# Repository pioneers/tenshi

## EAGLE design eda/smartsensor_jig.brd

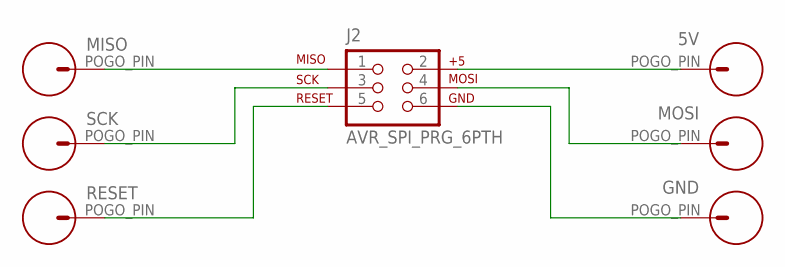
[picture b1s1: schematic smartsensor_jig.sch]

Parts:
5V: POGO_PIN; POGO_PIN_394
GND: POGO_PIN; POGO_PIN_394
J2: AVR_SPI_PRG_6PTH; 2X3
MISO: POGO_PIN; POGO_PIN_394
MOSI: POGO_PIN; POGO_PIN_394
RESET: POGO_PIN; POGO_PIN_394
SCK: POGO_PIN; POGO_PIN_394

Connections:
5V: 5V.POGO_PIN, J2.2
GND: GND.POGO_PIN, J2.6
MISO: J2.1, MISO.POGO_PIN
MOSI: J2.4, MOSI.POGO_PIN
RESET: J2.5, RESET.POGO_PIN
SCK: J2.3, SCK.POGO_PIN

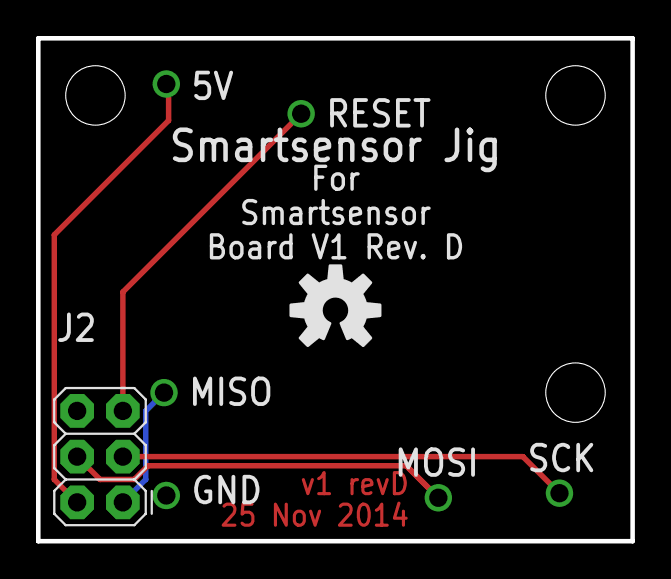
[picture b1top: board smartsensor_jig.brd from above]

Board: 2 copper layers, 33.0 x 27.9 mm, 12 parts (1 on the bottom side), 6 nets.

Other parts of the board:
U$1: OSHW-LOGO-M
U$2: PIE-LOGO-SMALL
U$3, U$4, U$5: STAND-OFF

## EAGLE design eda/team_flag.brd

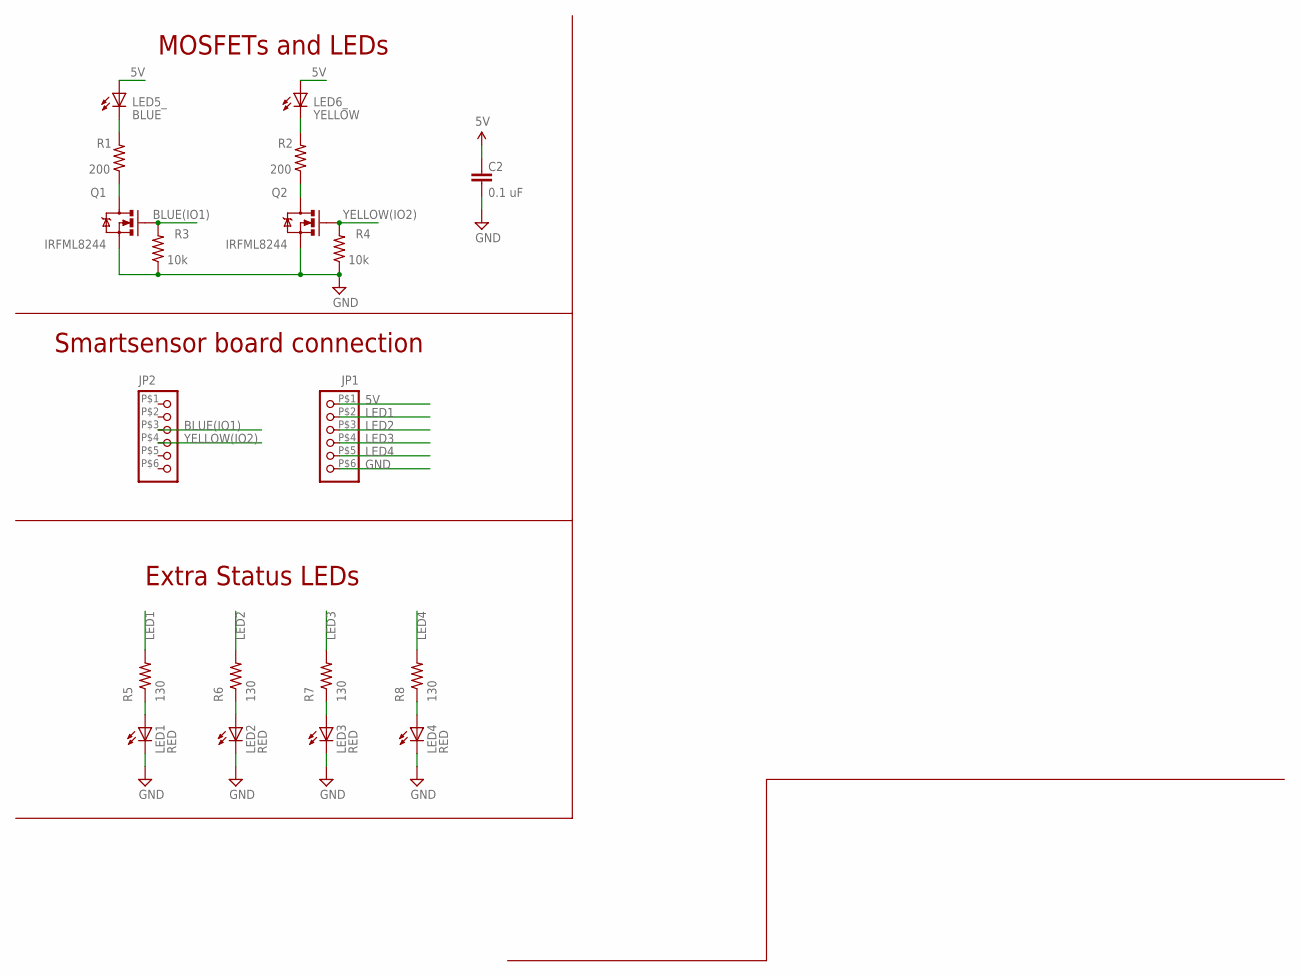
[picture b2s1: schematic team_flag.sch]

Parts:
C2: 0.1 uF; 0603-CAP
JP1, JP2: PINHD-1X6SMD-C; 1X06-SMD-C
LED1, LED2, LED3, LED4: RED; LED-0805
LED5_: BLUE; LED5MM-NOFLAT
LED6_: YELLOW; LED5MM-NOFLAT
Q1, Q2: IRFML8244; SOT23-3
R1, R2: 200; R0603
R3, R4: 10k; R0603
R5, R6, R7, R8: 130; R0603

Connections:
5V: C2.1, JP1.P$1 (1), LED5_.A, LED6_.A
BLUE(IO1): JP2.P$3 (3), Q1.1 (G), R3.2
BSOURCE: Q1.3 (D), R1.1
GND: C2.2, JP1.P$6 (6), LED1.C, LED2.C, LED3.C, LED4.C, Q1.2 (S), Q2.2 (S), R3.1, R4.1
LED1: JP1.P$2 (2), R5.2
LED2: JP1.P$3 (3), R6.2
LED3: JP1.P$4 (4), R7.2
LED4: JP1.P$5 (5), R8.2
unnamed: LED2.A, R6.1
unnamed: LED5_.K (C), R1.2
unnamed: LED6_.K (C), R2.2
unnamed: LED1.A, R5.1
unnamed: LED3.A, R7.1
unnamed: LED4.A, R8.1
YELLOW(IO2): JP2.P$4 (4), Q2.1 (G), R4.2
YSOURCE: Q2.3 (D), R2.1

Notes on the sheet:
MOSFETs and LEDs
Smartsensor board connection
Extra Status LEDs

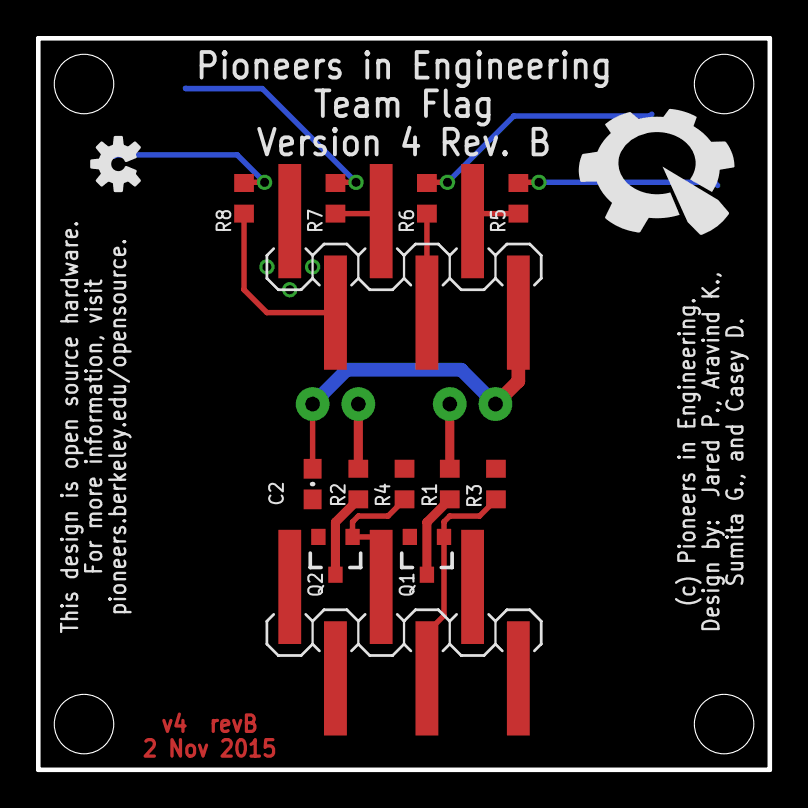
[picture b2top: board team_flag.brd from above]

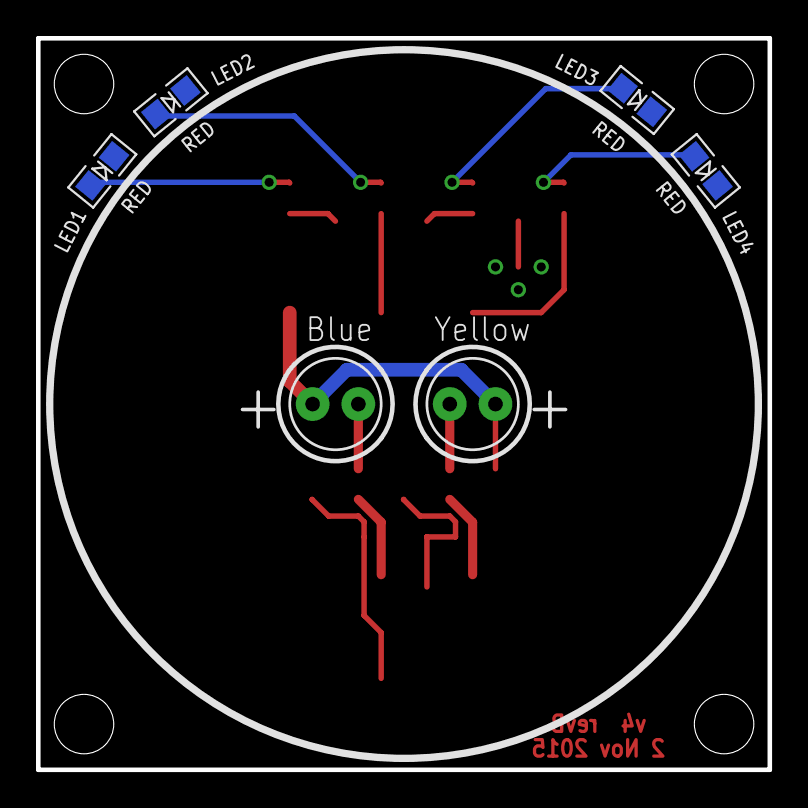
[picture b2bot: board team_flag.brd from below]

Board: 2 copper layers, 40.6 x 40.6 mm, 25 parts (6 on the bottom side), 16 nets.

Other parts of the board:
U$1: PIE-LOGO-SMALL
U$2: OSHW-LOGO-S
U$11, U$12, U$13, U$14: STAND-OFF

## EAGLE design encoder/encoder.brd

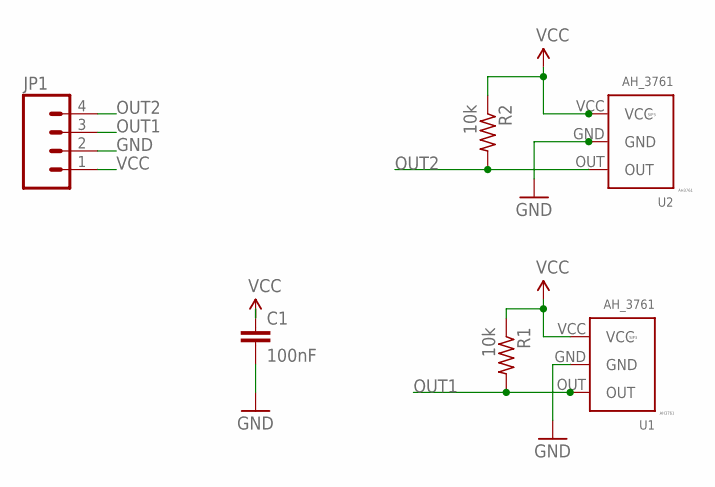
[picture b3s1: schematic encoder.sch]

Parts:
C1: 100nF; 0603-CAP
JP1: M04POLAR; MOLEX-1X4
R1, R2: 10k; R0603
U1, U2: AH_3761; SIP3

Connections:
GND: C1.2, JP1.2, U1.GND, U2.GND
OUT1: JP1.3, R1.2, U1.OUT
OUT2: JP1.4, R2.2, U2.OUT
VCC: C1.1, JP1.1, R1.1, R2.1, U1.VCC, U2.VCC

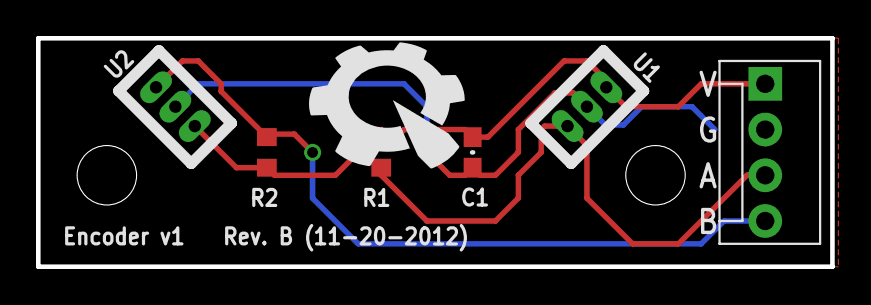
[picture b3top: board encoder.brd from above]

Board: 2 copper layers, 44.1 x 12.7 mm, 10 parts (1 on the bottom side), 4 nets.

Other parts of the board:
E$1, E$2: STAND-OFF
U$1: PIE-LOGO-SMALL
U$2: OSHW-LOGO-S

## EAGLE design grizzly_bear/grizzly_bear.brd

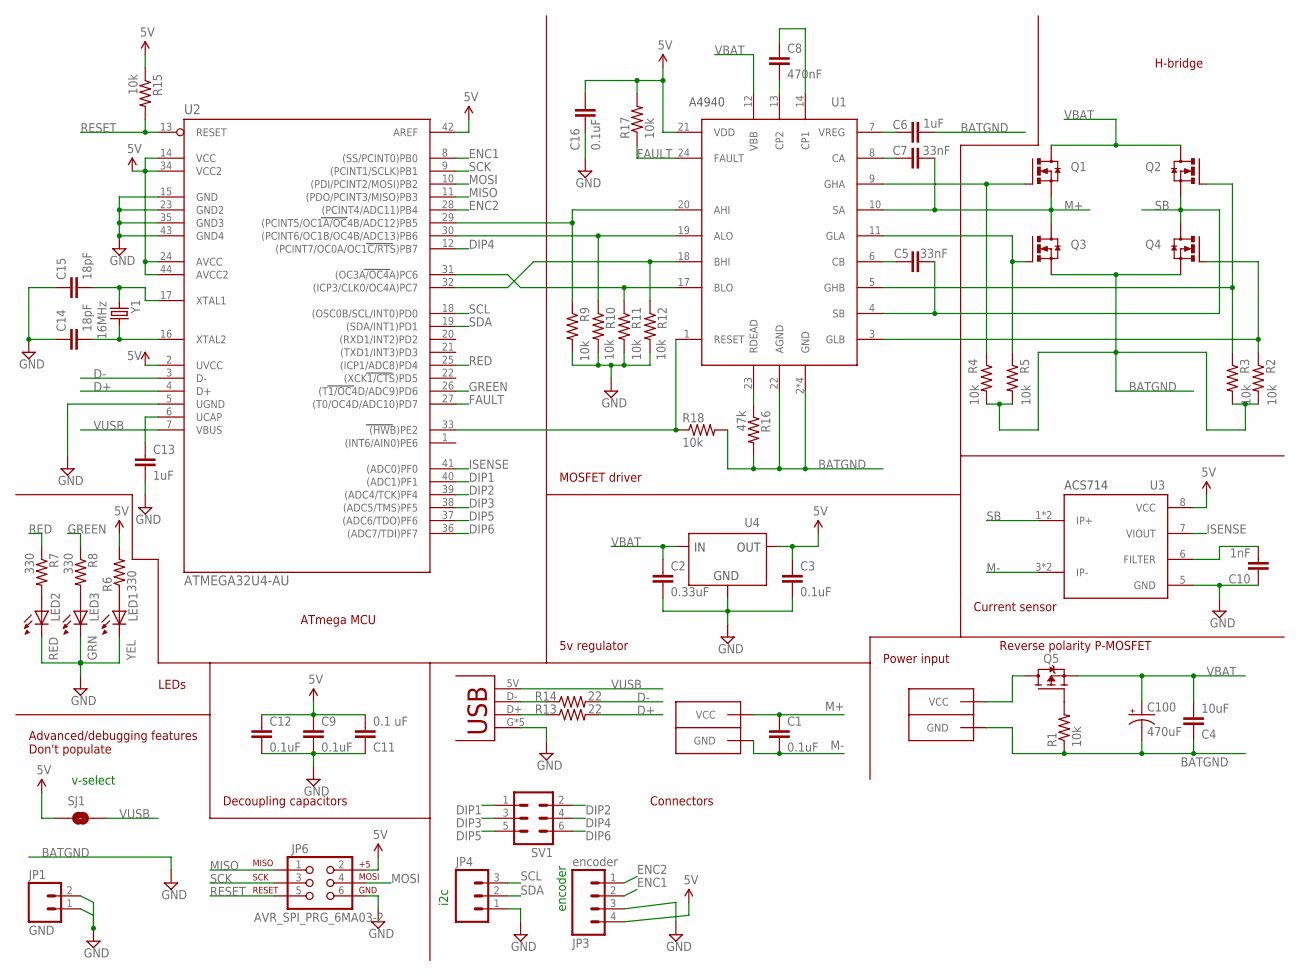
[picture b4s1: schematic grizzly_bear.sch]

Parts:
C1, C3, C9, C12, C16: 0.1uF; 0603-CAP
C2: 0.33uF; 0603-CAP
C4: 10uF; 0603-CAP
C5, C7: 33nF; 0603-CAP
C6, C13: 1uF; 0603-CAP
C8: 470nF; 0603-CAP
C10: 1nF; 0603-CAP
C11: 0.1 uF; 0603-CAP
C14, C15: 18pF; 0603-CAP
C100: 470uF; PANASONIC_G
JP1: GND; 1X02
JP3: encoder; 1X04-MTA
JP4: M031X03-MTA; 1X03-MTA
JP6: AVR_SPI_PRG_6MA03-2; MA03-2
LED1: YEL; LED-0805
LED2: RED; LED-0805
LED3: GRN; LED-0805
Q1, Q2, Q3, Q4: N-CHANNEL-MOSFET; SOT669
Q5: IPD90P03P4L; TO252
R1, R2, R3, R4, R5, R9, R10, R11, R12, R15, R17, R18: 10k; R0603
R6, R7, R8: 330; R0603
R13, R14: 22; R0603
R16: 47k; R0603
SJ1: SOLDERJUMPERNO; SJ_2S-NO
SV1: MA03-2
U1: A4940; 24-PIN_TSSOP
U2: ATMEGA32U4-AU; TQFP44
U3: ACS714; 8-PIN_SOIC
U4: UA78L00; SOT-89-3
U$2: USB-M26FTR
U$18, U$19: ANDERSONVERTICAL; ANDERSON_VERTICAL
Y1: 16MHz; HC49UP

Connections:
5V: C3.1, C9.1, C11.2, C12.1, C16.1, JP3.4, JP6.2, R6.2, R15.1, R17.2, SJ1.1, U1.21 (VDD), U2.2 (UVCC), U2.14 (VCC), U2.24 (AVCC), U2.34 (VCC2), U2.42 (AREF), U2.44 (AVCC2), U3.8 (VCC), U4.OUTPUT (OUT); also elsewhere on the board
AHI: R9.1, U1.20 (AHI), U2.29 ((PCINT5/OC1A/OC4B/ADC12)PB5)
ALO: R10.1, U1.19 (ALO), U2.30 ((PCINT6/OC1B/OC4B/ADC13)PB6)
BHI: R12.1, U1.18 (BHI), U2.32 ((ICP3/CLK0/OC4A)PC7)
BLO: R11.1, U1.17 (BLO), U2.31 ((OC3A/OC4A)PC6)
CA: C7.1, U1.8 (CA)
CB: C5.2, U1.6 (CB)
CP1: C8.1, U1.14 (CP1)
CP2: C8.2, U1.13 (CP2)
D+: R13.2, U2.4 (D+)
D+-_CON: R13.1, U$2.D+
D-: R14.2, U2.3 (D-)
D-_CON: R14.1, U$2.D-
DE: U2.1 ((INT6/AIN0)PE6); also elsewhere on the board
DIP1: SV1.1, U2.40 ((ADC1)PF1)
DIP2: SV1.2, U2.39 ((ADC4/TCK)PF4)
DIP3: SV1.3, U2.38 ((ADC5/TMS)PF5)
DIP4: SV1.4, U2.12 ((PCINT7/OC0A/OC1C/RTS)PB7)
DIP5: SV1.5, U2.37 ((ADC6/TDO)PF6)
DIP6: SV1.6, U2.36 ((ADC7/TDI)PF7)
DRIVER-RESET: R18.1, U1.1 (RESET), U2.33 ((HWB)PE2)
ENC1: JP3.2, U2.8 ((SS/PCINT0)PB0)
ENC2: JP3.1, U2.28 ((PCINT4/ADC11)PB4)
FAULT: R17.1, U1.24 (FAULT), U2.27 ((T0/OC4D/ADC10)PD7)
FILTER: C10.2, U3.6 (FILTER)
GHA: Q1.4 (G), R4.1, U1.9 (GHA)
GHB: Q2.4 (G), R3.1, U1.5 (GHB)
GLA: Q3.4 (G), R5.1, U1.11 (GLA)
GLB: Q4.4 (G), R2.1, U1.3 (GLB)
GND: C2.2, C3.2, C4.1, C6.2, C9.2, C10.1, C11.1, C12.2, C13.2, C14.1, C15.1, C16.2, C100.-, JP1.1, JP1.2, JP3.3, JP4.1, JP6.6, LED1.C, LED2.C, LED3.C, Q3.1 (S), Q3.2 (S), Q3.3 (S), Q4.1 (S), Q4.2 (S), Q4.3 (S), R1.1, R2.2, R3.2, R4.2, R5.2, R9.2, R10.2, R11.2, R12.2, R16.2, R18.2, U1.2 (GND), U1.15 (GND), U1.16 (GND), U1.22 (AGND), U1.PAD (GND), U2.5 (UGND), U2.15 (GND), U2.23 (GND2), U2.35 (GND3), U2.43 (GND4), U3.5 (GND), U4.COMMON (GND), U$2.G, U$2.S1 (G), U$2.S2 (G), U$2.S3 (G), U$2.S4 (G), U$18.PIN1 (GND); also elsewhere on the board
GREEN: R8.1, U2.26 ((T1/OC4D/ADC9)PD6)
GREEN-LED: LED3.A, R8.2
ISENSE: U2.41 ((ADC0)PF0), U3.7 (VIOUT)
M+: C1.1, C7.2, Q1.1 (S), Q1.2 (S), Q1.3 (S), Q3.MB (D), U1.10 (SA), U$19.PIN2 (VCC)
M-: C1.2, U3.3 (IP-), U3.4 (IP-), U$19.PIN1 (GND)
MISO: JP6.1, U2.11 ((PDO/PCINT3/MISO)PB3)
MOSI: JP6.4, U2.10 ((PDI/PCINT2/MOSI)PB2)
POWER-LED: LED1.A, R6.1
RDEAD: R16.1, U1.23 (RDEAD)
RE: U2.22 ((XCK1/CTS)PD5); also elsewhere on the board
RED: R7.1, U2.25 ((ICP1/ADC8)PD4)
RED-LED: LED2.A, R7.2
RESET: JP6.5, R15.2, U2.13 (RESET)
RPP-GATE: Q5.1 (G), R1.2
RXD1: U2.20 ((RXD1/INT2)PD2); also elsewhere on the board
SB: C5.1, Q2.1 (S), Q2.2 (S), Q2.3 (S), Q4.MB (D), U1.4 (SB), U3.1 (IP+), U3.2 (IP+)
SCK: JP6.3, U2.9 ((PCINT1/SCLK)PB1)
SCL: JP4.3, U2.18 ((OSC0B/SCL/INT0)PD0)
SDA: JP4.2, U2.19 ((SDA/INT1)PD1)
TXD1: U2.21 ((TXD1/INT3)PD3); also elsewhere on the board
UCAP: C13.1, U2.6 (UCAP)
VBAT: C2.1, C4.2, C100.+, Q1.MB (D), Q2.MB (D), Q5.2 (S), U1.12 (VBB), U4.INPUT (IN)
VIN: Q5.3 (D), U$18.PIN2 (VCC)
VREG: C6.1, U1.7 (VREG)
VUSB: SJ1.2, U2.7 (VBUS), U$2.5V
XTAL1: C15.2, U2.17 (XTAL1), Y1.2
XTAL2: C14.2, U2.16 (XTAL2), Y1.1

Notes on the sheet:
v-select
i2c
encoder
Advanced/debugging features Don't populate
Connectors
Decoupling capacitors
LEDs
ATmega MCU
MOSFET driver
H-bridge
Current sensor
5v regulator
Power input
Reverse polarity P-MOSFET

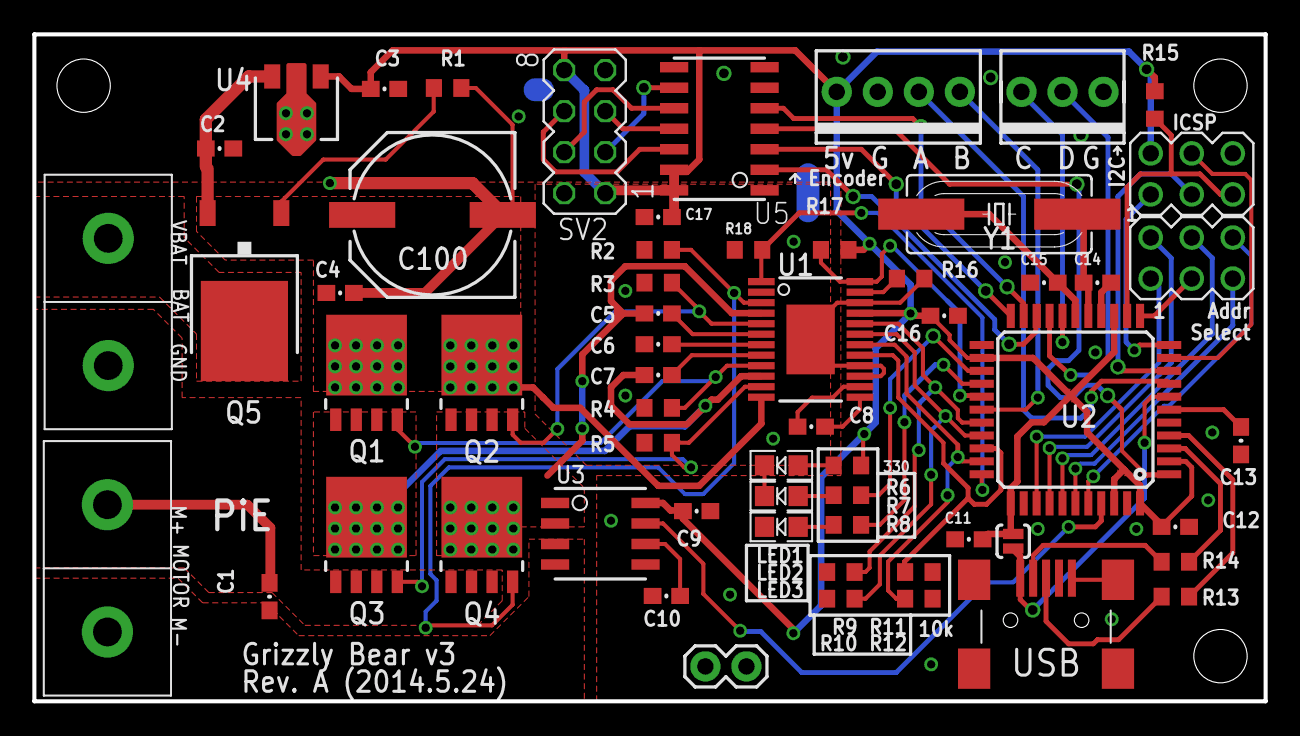
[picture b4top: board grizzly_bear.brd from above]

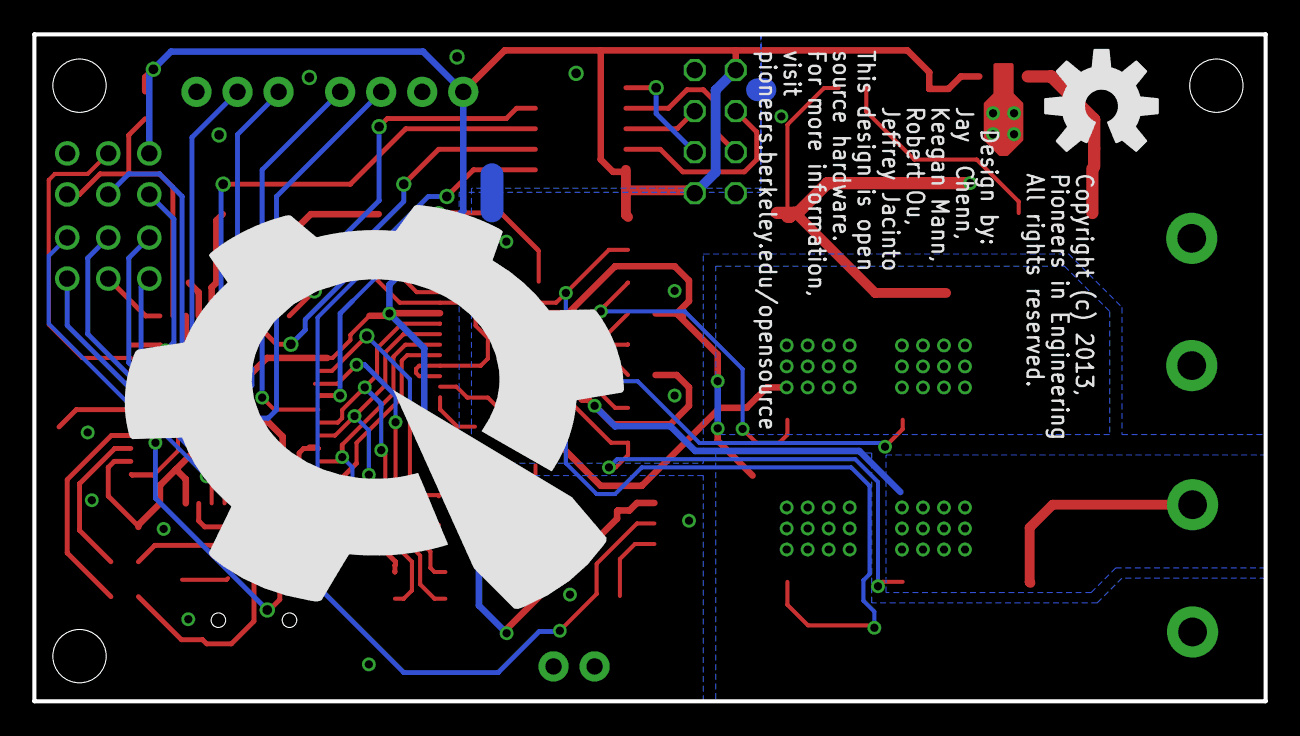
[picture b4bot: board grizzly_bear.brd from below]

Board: 2 copper layers, 76.2 x 41.3 mm, 65 parts (2 on the bottom side), 61 nets.

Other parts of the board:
C17: 0.1uF; 0603-CAP
STANDOFF1, STANDOFF2, STANDOFF3: STAND-OFF
SV2: MA04-2
U5: ISL83491SOIC; SOIC14
U$1: OSHW-LOGO-L
U$17: PIE-LOGO

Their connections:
5V: C17.1, SV2.1, SV2.8, U5.13, U5.14; also elsewhere on the board
A+: SV2.6, U5.12
A-: SV2.5, U5.11
B+: SV2.3, U5.9
B-: SV2.4, U5.10
DE: U5.4; also elsewhere on the board
GND: C17.2, SV2.2, SV2.7, U5.6, U5.7; also elsewhere on the board
RE: U5.3; also elsewhere on the board
RXD1: U5.2; also elsewhere on the board
TXD1: U5.5; also elsewhere on the board

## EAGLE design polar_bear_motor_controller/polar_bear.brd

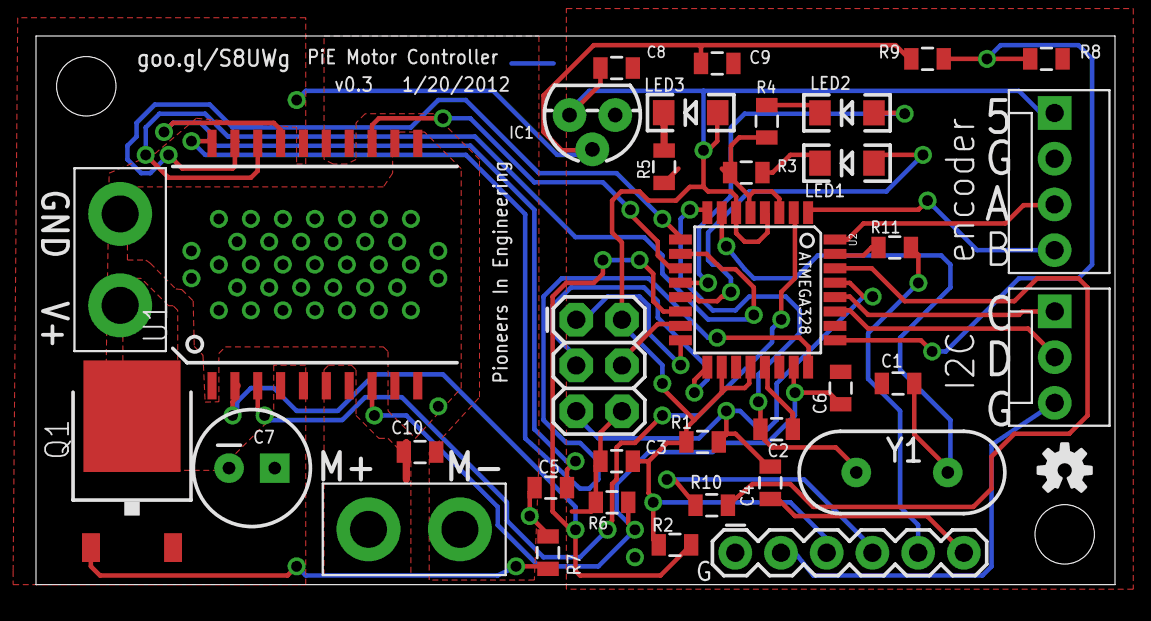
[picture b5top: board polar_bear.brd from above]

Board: 2 copper layers, 59.9 x 30.5 mm, 39 parts (1 on the bottom side), 37 nets.

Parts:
C1, C2: 18pF; 0805
C3, C4, C8, C9: 0.1UF; 0805
C5: 33NF; 0805
C6: 1UF; 0805
C7: 100uF; CPOL-RADIAL-100UF-25V
C10: 0.1uF; 0805
IC1: TO-92
J1: AVR_SPI_PRG_6PTH; 2X3
JP1, JP2: 1X02_XTRA_BIG
JP3: MOLEX-1X3
JP4: MOLEX-1X4
JP5: 1X06
LED1: GREEN; LED-1206
LED2: RED; LED-1206
LED3: YELLOW; LED-1206
Q1: AOD417; TO252
R1, R2, R7: 10K; 0805
R3, R4, R5: 330; 0805
R6: 100; 0805
R8: 4K; 0805
R9, R10, R11: 1K; 0805
SJ1: SOLDERJUMPERNO; SJ_2S-NO
U1: MC33887; HSOP-20
U2: ATMEGA168; TQFP32-08
U$3, U$11: STAND-OFF
U$12: OSHW-LOGOS; OSHW-LOGO-S
Y1: 16MHZ; HC49US

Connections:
5V: C3.2, C8.2, IC1.3, J1.2, JP4.1, JP5.3, LED3.A, R1.2, R2.2, U2.4, U2.6, U2.18, U2.20
BATGND: C5.1, C7.2, JP1.2, R7.1, SJ1.2, U1.1, U1.9, U1.10, U1.11, U1.12
D1: U1.18, U2.10
D2: U1.13, U2.11
DTR: C4.1, JP5.6
EN: U1.20, U2.24
ENC1: JP4.3, U2.32
ENC2: JP4.4, U2.1
FB: C6.1, R6.2, U1.8, U2.23
FS: R2.1, U1.2, U2.14
GND: C1.1, C2.1, C3.1, C6.2, C8.1, C9.1, IC1.1, J1.6, JP3.3, JP4.2, JP5.1, JP5.2, R3.1, R4.1, R5.1, R6.1, R8.2, SJ1.1, U2.3, U2.5, U2.21
IN1: U1.3, U2.2
IN2: U1.19, U2.9
M+: C10.2, JP2.1, U1.6, U1.7
M-: C10.1, JP2.2, U1.14, U1.15
MISO: J1.1, U2.16
MOSI: J1.4, U2.15
unnamed: LED1.A, U2.13
unnamed: C2.2, U2.8, Y1.1
unnamed: C1.2, U2.7, Y1.2
unnamed: LED2.A, U2.12
unnamed: LED1.C, R3.2
unnamed: LED2.C, R4.2
unnamed: C5.2, U1.17
unnamed: Q1.1, R7.2
unnamed: LED3.C, R5.2
unnamed: R8.1, R9.2, U2.25
unnamed: R11.2, U2.31
unnamed: R10.2, U2.30
RESET: C4.2, J1.5, R1.1, U2.29
RX: JP5.4, R10.1
SCK: J1.3, U2.17
SCL: JP3.1, U2.28
SDA: JP3.2, U2.27
TX: JP5.5, R11.1
VBAT: C7.1, C9.2, IC1.2, Q1.2, R9.1, U1.4, U1.5, U1.16
VRAW: JP1.1, Q1.3

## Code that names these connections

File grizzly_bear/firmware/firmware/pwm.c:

// Licensed to Pioneers in Engineering under one
// or more contributor license agreements.  See the NOTICE file
// distributed with this work for additional information
// regarding copyright ownership.  Pioneers in Engineering licenses
// this file to you under the Apache License, Version 2.0 (the
// "License"); you may not use this file except in compliance
//  with the License.  You may obtain a copy of the License at
//
//    http://www.apache.org/licenses/LICENSE-2.0
//
// Unless required by applicable law or agreed to in writing,
// software distributed under the License is distributed on an
// "AS IS" BASIS, WITHOUT WARRANTIES OR CONDITIONS OF ANY
// KIND, either express or implied.  See the License for the
// specific language governing permissions and limitations
// under the License

#include "pwm.h"

#include <avr/io.h>

#include "pindef.h"

// WARNING: THIS FILE IS WIP!

void init_pwm(void) {
  // Keep high side driver in reset.
  driver_enable(0);
  DDR(PINDEF_HIGHSIDEENABLE) |= _BV(IO(PINDEF_HIGHSIDEENABLE));

  // dead time
  DT4 = 0;

  // Enable enhanced mode.
  TCCR4E = _BV(ENHC4);

  // Clear count.
  TC4H = 0;
  TCNT4 = 0;

  // Set compare c to max.
  TC4H = 7;
  OCR4C = 0xFF;

  // Enable phase and frequency correct pwm mode.
  TCCR4D = _BV(WGM40);
  // Disable compare d.
  TCCR4C = 0;

  // Prescale by 8.
  TCCR4B = _BV(CS42);
}

void driver_enable(unsigned char enable) {
  if (enable)
    PORT(PINDEF_HIGHSIDEENABLE) |= _BV(IO(PINDEF_HIGHSIDEENABLE));
  else {
    // Reset high side driver.
    PORT(PINDEF_HIGHSIDEENABLE) &= ~(_BV(IO(PINDEF_HIGHSIDEENABLE)));

    // Configure pins as outputs, 0 by default.
    PORTB &= ~(_BV(PB5) | _BV(PB6));
    DDRB |= (_BV(PB5) | _BV(PB6));
    PORTC &= ~(_BV(PC6) | _BV(PC7));
    DDRC |= (_BV(PC6) | _BV(PC7));

    // Enable pwm mode, do not connect pins.
    TCCR4A = _BV(PWM4A) | _BV(PWM4B);
  }
}

void set_pwm_val(unsigned int val) {
  TCCR4E |= _BV(TLOCK4);
  TC4H = (val >> 8) & 7;
  OCR4A = val;
  OCR4B = val;
  TCCR4E &= ~(_BV(TLOCK4));
}

void set_sign_magnitude_go_brake_fwd(void) {
  // Fix side b to have top off and bottom on.
  PORTC = (PORTC & ~(_BV(PC7))) | _BV(PC6);
  // Clear the other output.
  PORTB &= ~(_BV(PB5) | _BV(PB6));
  // Make side b output
  DDRC |= (_BV(PC6) | _BV(PC7));
  // Make both pins on side a output
  DDRB |= (_BV(PB6) | _BV(PB5));
  // Invert output
  TCCR4B |= _BV(PWM4X);
  // Connect side a to pwm.
  TCCR4A = _BV(COM4B0) | _BV(PWM4A) | _BV(PWM4B);
}

void set_sign_magnitude_go_brake_bck(void) {
  // Fix side a to have top off and bottom on.
  PORTB = (PORTB & ~(_BV(PB5))) | _BV(PB6);
  // Clear the other output.
  PORTC &= ~(_BV(PC6) | _BV(PC7));
  // Make all outputs
  DDRB |= (_BV(PB5) | _BV(PB6));
  DDRC |= (_BV(PC6) | _BV(PC7));
  // Do not invert output
  TCCR4B &= ~(_BV(PWM4X));
  // Connect side b to pwm.
  TCCR4A = _BV(COM4A0) | _BV(PWM4A) | _BV(PWM4B);
}

void set_sign_magnitude_go_coast_fwd(void) {
  // Clear all outputs
  PORTC &= ~(_BV(PC7) | _BV(PC6));
  PORTB &= ~(_BV(PB5) | _BV(PB6));
  
  // Make only Low B side output. Let High side be pulled down.
  DDRC = ((DDRC & ~(_BV(PC7))) | _BV(PC6));
  // Make only High A side output. Let Low side be pulled down.
  DDRB = ((DDRB & ~(_BV(PB6))) | _BV(PB5));
  
  // Invert output
  TCCR4B |= _BV(PWM4X);
  // Connect High A and Low B side to pwm.
  TCCR4A =  _BV(COM4A0) | _BV(COM4B0) | _BV(PWM4A) | _BV(PWM4B);
}

void set_sign_magnitude_go_coast_bck(void) {
  // Clear all ouptuts.
  PORTB &= ~(_BV(PB5) | _BV(PB6));
  PORTC &= ~(_BV(PC6) | _BV(PC7));
  
  // Make only Low A side output. Let High side be pulled down.
  DDRB = ((DDRB & ~(_BV(PB5))) | _BV(PB6));
  // Make only High B side output. Let Low side be pulled down.
  DDRC = ((DDRC & ~(_BV(PC6))) | _BV(PC7));
  
  // Do not invert output
  TCCR4B &= ~(_BV(PWM4X));
  // Connect side b HIGH ONLY to pwm.
  TCCR4A = _BV(COM4A1) | _BV(COM4B1) | _BV(PWM4A) | _BV(PWM4B);
}

void set_locked_antiphase(void) {
  // Make all outputs
  DDRB |= (_BV(PB5) | _BV(PB6));
  DDRC |= (_BV(PC6) | _BV(PC7));
  // Invert output
  TCCR4B |= _BV(PWM4X);
  // Connect side a and side b to pwm.
  TCCR4A = _BV(COM4A0) | _BV(COM4B0) | _BV(PWM4A) | _BV(PWM4B);
}

void set_controlled_brake(void) {
  // Clear all outputs
  PORTC &= ~(_BV(PC7) | _BV(PC6));
  PORTB &= ~(_BV(PB5) | _BV(PB6));
  
  // Make Low B side output.
  DDRC = ((DDRC & ~(_BV(PC7))) | _BV(PC6));
  // Make Low A side output.
  DDRB = ((DDRB & ~(_BV(PB5))) | _BV(PB6));
  
  // Invert output
  TCCR4B |= _BV(PWM4X);
  // Connect Low side A as inverted pwm. Connect Low side B as inverted pwm.
  TCCR4A = _BV(COM4A0) | _BV(COM4B0) | _BV(COM4B1) | _BV(PWM4A) | _BV(PWM4B);
}

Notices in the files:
encoder/encoder.brd:
Copyright (c) 2013, Pioneers in Engineering
All rights reserved.
parts and their libraries:
SparkFun-Connectors: Licensing: Creative Commons ShareAlike 4.0 International - https://creativecommons.org/licenses/by-sa/4.0
SparkFun-Electromechanical: Licensing: CC v3.0 Share-Alike You are welcome to use this library for commercial purposes.
